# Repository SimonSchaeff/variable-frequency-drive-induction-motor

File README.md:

# Frequency Inverter – University Project

This repository contains the development files for a custom-built frequency inverter developed as part of a university project at Munich University of Applied Sciences (Hochschule München).

The power electronics and control electronics were designed using KiCad. The corresponding hardware design files are located in the `hardware/` directory. The software is based on an STM32 microcontroller, and the firmware source code is available in the `source_code/` directory.

The frequency inverter is designed to control asynchronous motors with a power rating of up to 3 kW. The operating frequency can be set within a range of 0 to 99 Hz, either manually using a potentiometer or wirelessly via a Bluetooth-enabled smartphone application. The application is located in the `smartphone_app/` directory.

## Disclaimer

This project is intended for educational and engineering development purposes. No warranty is provided regarding the functionality, safety, or suitability of the design for a particular application.

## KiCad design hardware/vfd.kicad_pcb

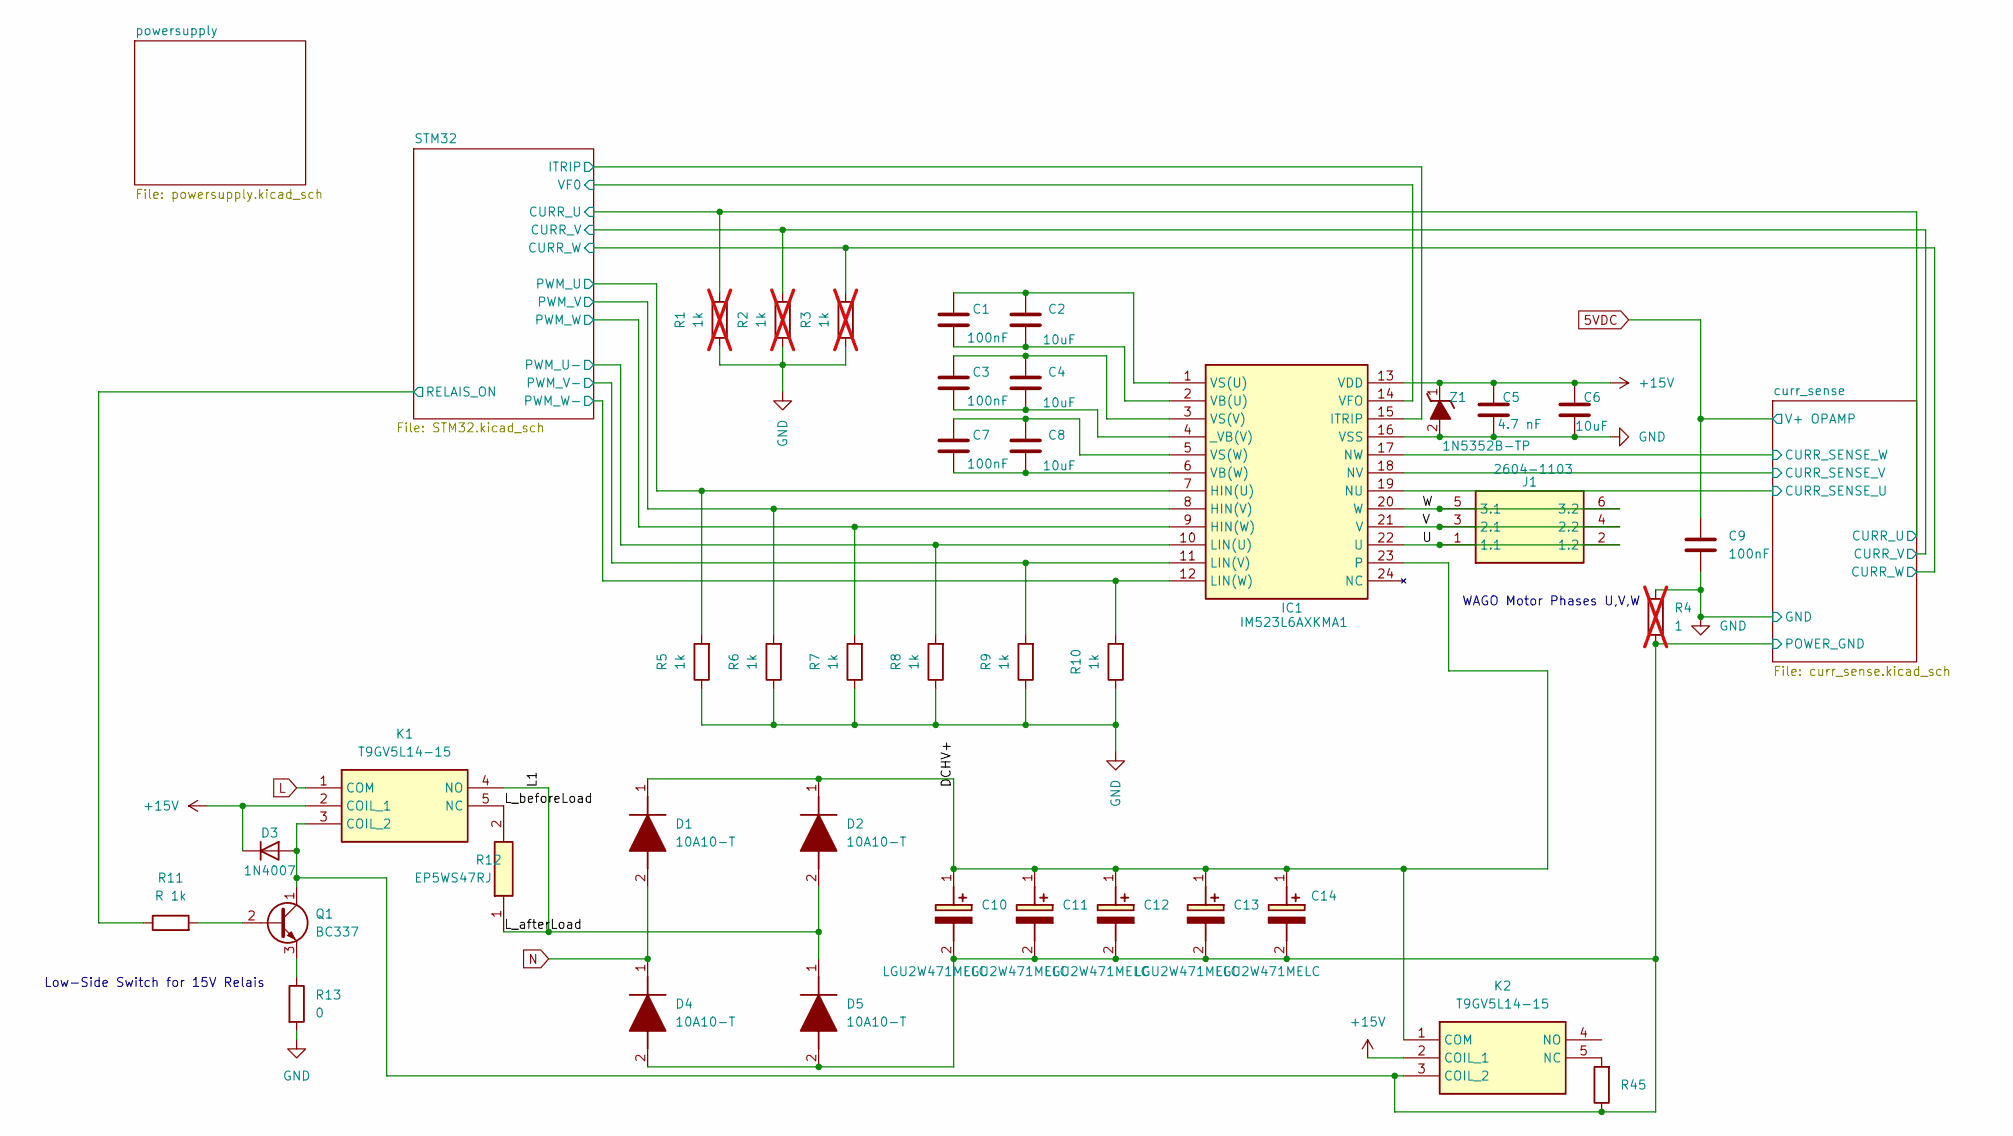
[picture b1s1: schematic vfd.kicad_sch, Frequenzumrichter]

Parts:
C1, C3, C7, C9: 100nF; C_0603_1608Metric
C2, C4, C6, C8: 10uF; C_1206_3216Metric
C5: 4.7 nF; C_0603_1608Metric
C10, C11, C12, C13, C14: LGU2W471MELC; CAPPRD1000W190D3550H5200; Mouser Part Number 647-LGU2W471MELC
D1, D2, D4, D5: 10A10-T; DIOAD4425W130L885D885; Mouser Part Number 583-10A10
D3: 1N4007; D_DO-41_SOD81_P10.16mm_Horizontal
IC1: IM523L6AXKMA1; Manufacturer_Part_Number IM523L6AXKMA1; Mouser Part Number 726-IM523L6AXKMA1
J1: 2604-1103; 26041103; Manufacturer_Part_Number 2604-1103
K1, K2: T9GV5L14-15; T9GV5L1415; Mouser Part Number 655-T9GV5L14-15
Q1: BC337; TO-92_Inline
R1, R2, R3: 1k; R_0603_1608Metric; not fitted
R4: 1; R_0603_1608Metric; not fitted
R5, R6, R7, R8, R9, R10: 1k; R_0603_1608Metric
R11: R 1k; R_0603_1608Metric
R12: EP5WS47RJ; RESAD5900W80L2500D850; Manufacturer_Part_Number EP5WS47RJ; Mouser Part Number 279-EP5WS47RJ
R13: 0; R_0603_1608Metric
R45: R_0603_1608Metric
Z1: 1N5352B-TP; DIOAD1910W90L670D310; Mouser Part Number 833-1N5352B-TP

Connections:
5VDC: C9.1; also elsewhere on the board
+15V: C5.1, C6.1, D3.1 (K), IC1.13 (VDD), K1.2 (COIL_1), K2.2 (COIL_1), Z1.1 (K); also elsewhere on the board
/DCHV+: C10.1 (+), C11.1 (+), C12.1 (+), C13.1 (+), C14.1 (+), D1.1 (K), D2.1 (K), IC1.23, K2.1 (COM)
/L1: D2.2 (A), D5.1 (K), K1.4 (NO), R12.1
/L_beforeLoad: K1.5 (NC), R12.2
/STM32/CURR_U: R1.2; also elsewhere on the board
/STM32/CURR_V: R2.2; also elsewhere on the board
/STM32/CURR_W: R3.2; also elsewhere on the board
/STM32/ITRIP: IC1.15 (ITRIP); also elsewhere on the board
/STM32/PWM_U: IC1.7 (HIN(U)), R5.2; also elsewhere on the board
/STM32/PWM_U-: IC1.10 (LIN(U)), R8.2; also elsewhere on the board
/STM32/PWM_V: IC1.8 (HIN(V)), R6.2; also elsewhere on the board
/STM32/PWM_V-: IC1.11 (LIN(V)), R9.2; also elsewhere on the board
/STM32/PWM_W: IC1.9 (HIN(W)), R7.2; also elsewhere on the board
/STM32/PWM_W-: IC1.12 (LIN(W)), R10.2; also elsewhere on the board
/STM32/RELAIS_ON: R11.1; also elsewhere on the board
/STM32/VF0: IC1.14 (VFO); also elsewhere on the board
/U: IC1.22 (U), J1.1 (1.1), J1.2 (1.2)
/V: IC1.21 (V), J1.3 (2.1), J1.4 (2.2)
/W: IC1.20 (W), J1.5 (3.1), J1.6 (3.2)
/curr_sense/CURR_SENSE_U: IC1.19 (NU); also elsewhere on the board
/curr_sense/CURR_SENSE_V: IC1.18 (NV); also elsewhere on the board
/curr_sense/CURR_SENSE_W: IC1.17 (NW); also elsewhere on the board
GND: C5.2, C6.2, C9.2, IC1.16 (VSS), R1.1, R2.1, R3.1, R4.2, R5.1, R6.1, R7.1, R8.1, R9.1, R10.1, R13.2, Z1.2 (A); also elsewhere on the board
L: K1.1 (COM); also elsewhere on the board
N: D1.2 (A), D4.1 (K); also elsewhere on the board
unnamed: C1.2, C2.2, IC1.2 (VB(U))
unnamed: C7.2, C8.2, IC1.6 (VB(W))
unnamed: C1.1, C2.1, IC1.1 (VS(U))
unnamed: C3.1, C4.1, IC1.3 (VS(V))
unnamed: C7.1, C8.1, IC1.5 (VS(W))
unnamed: C3.2, C4.2, IC1.4 (_VB(V))
unnamed: K2.5 (NC), R45.2
unnamed: Q1.2 (B), R11.2
unnamed: Q1.3 (E), R13.1

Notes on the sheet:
WAGO Motor Phases U,V,W
Low-Side Switch for 15V Relais

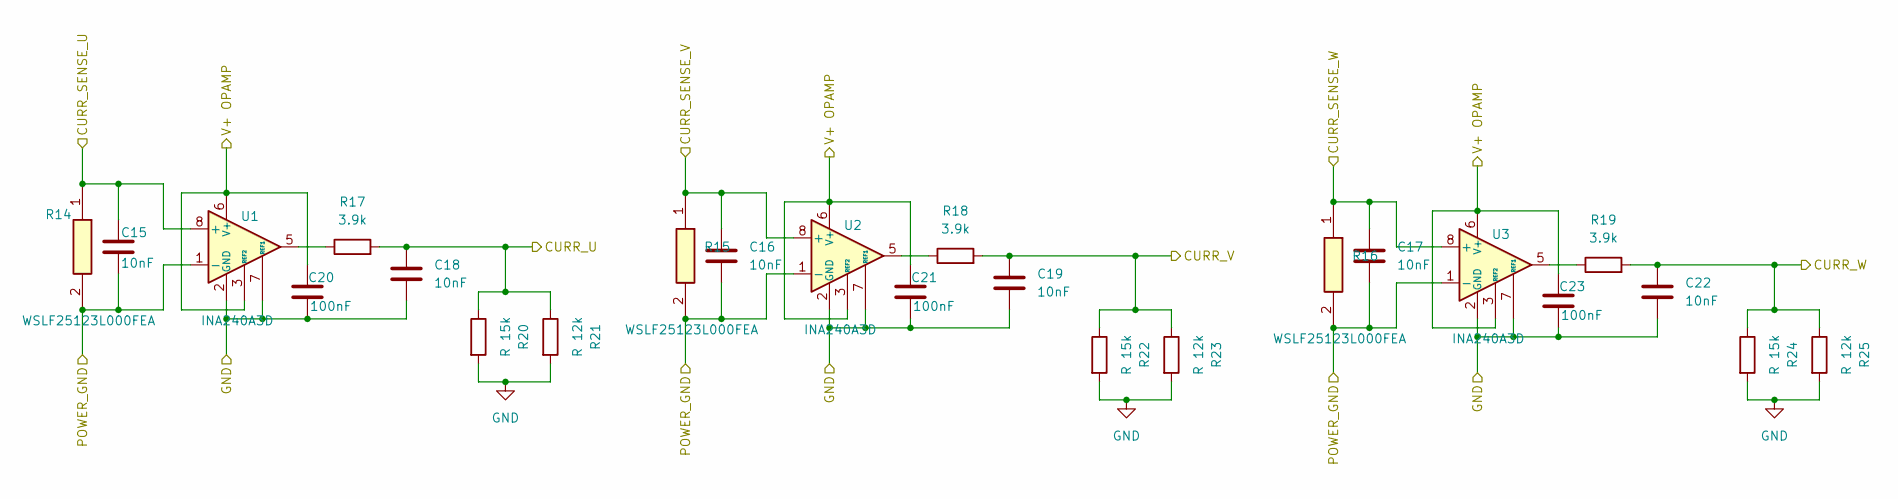
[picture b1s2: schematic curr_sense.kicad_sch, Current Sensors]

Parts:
C15, C16, C17, C18, C19, C22: 10nF; C_0603_1608Metric
C20, C21, C23: 100nF; C_0603_1608Metric
R14, R15, R16: WSLF25123L000FEA; RESC6430X48N; Mouser Part Number 71-WSLF25123L000FEA
R17, R18, R19: 3.9k; R_0603_1608Metric
R20, R22, R24: R 15k; R_0603_1608Metric
R21, R23, R25: R 12k; R_0603_1608Metric
U1, U2, U3: INA240A3D; SOIC-8_3.9x4.9mm_P1.27mm

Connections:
5VDC: C20.1, C21.1, C23.1, U1.3 (REF2), U1.6 (V+), U2.3 (REF2), U2.6 (V+), U3.3 (REF2), U3.6 (V+); also elsewhere on the board
/STM32/CURR_U: C18.1, R17.2, R20.1, R21.1; also elsewhere on the board
/STM32/CURR_V: C19.1, R18.2, R22.1, R23.1; also elsewhere on the board
/STM32/CURR_W: C22.1, R19.2, R24.1, R25.1; also elsewhere on the board
/curr_sense/CURR_SENSE_U: C15.1, R14.1, U1.8 (+); also elsewhere on the board
/curr_sense/CURR_SENSE_V: C16.1, R15.1, U2.8 (+); also elsewhere on the board
/curr_sense/CURR_SENSE_W: C17.1, R16.1, U3.8 (+); also elsewhere on the board
GND: C18.2, C19.2, C20.2, C21.2, C22.2, C23.2, R20.2, R21.2, R22.2, R23.2, R24.2, R25.2, U1.2 (GND), U1.4 (GND), U1.7 (REF1), U2.2 (GND), U2.4 (GND), U2.7 (REF1), U3.2 (GND), U3.4 (GND), U3.7 (REF1); also elsewhere on the board
unnamed: R17.1, U1.5
unnamed: R18.1, U2.5
unnamed: R19.1, U3.5

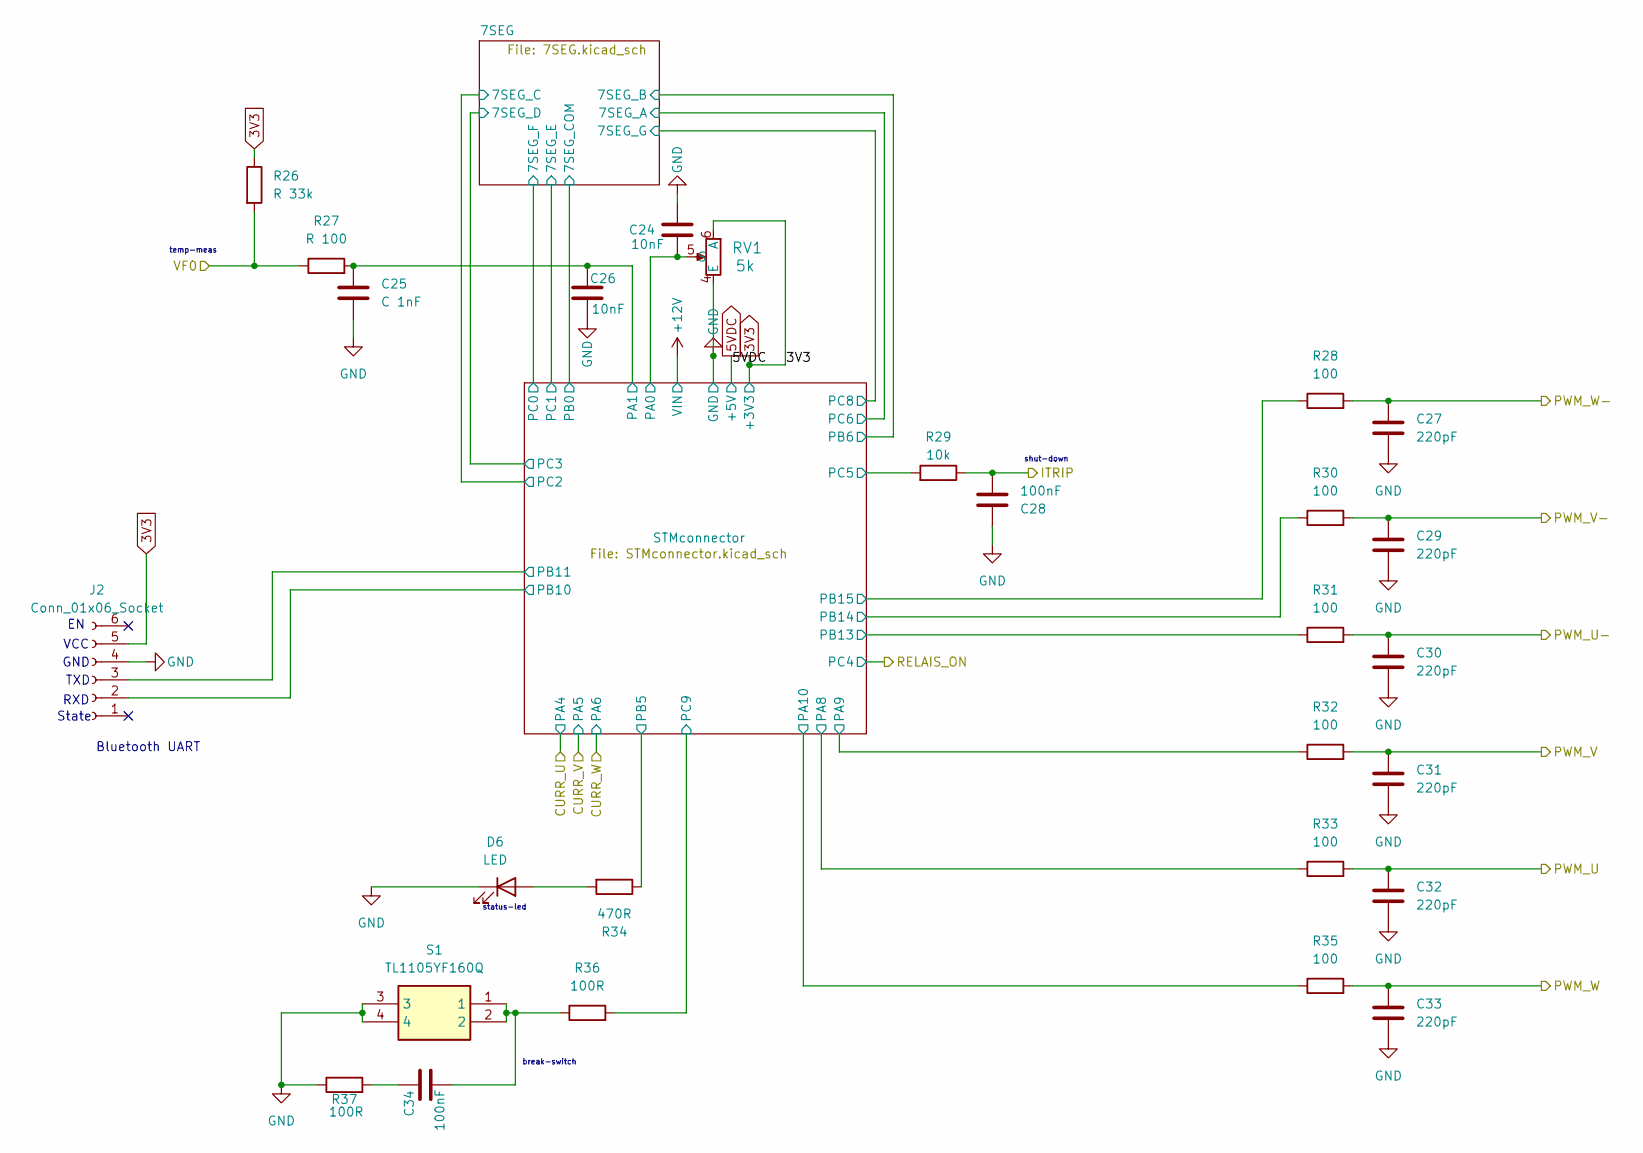
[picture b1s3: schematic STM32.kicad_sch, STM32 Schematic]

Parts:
C24, C26: 10nF; C_0603_1608Metric
C25: C 1nF; C_0603_1608Metric
C27, C29, C30, C31, C32, C33: 220pF; C_0603_1608Metric
C28, C34: 100nF; C_0603_1608Metric
D6: LED; LED_0805_2012Metric
J2: Conn_01x06_Socket; PinSocket_1x06_P2.54mm_Vertical
R26: R 33k; R_0603_1608Metric
R27: R 100; R_0603_1608Metric
R28, R30, R31, R32, R33, R35: 100; R_0603_1608Metric
R29: 10k; R_0603_1608Metric
R34: 470R; R_0603_1608Metric
R36, R37: 100R; R_0603_1608Metric
RV1: 5k; PC16SV-10IP06-103A2020-TA_PHR
S1: TL1105YF160Q; Mouser Part Number 612-TL1105YF160Q

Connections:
3V3: J2.5, R26.1, RV1.6 (A); also elsewhere on the board
/STM32/ITRIP: C28.2, R29.1; also elsewhere on the board
/STM32/PWM_U: C32.1, R33.2; also elsewhere on the board
/STM32/PWM_U-: C30.1, R31.2; also elsewhere on the board
/STM32/PWM_V: C31.1, R32.2; also elsewhere on the board
/STM32/PWM_V-: C29.1, R30.2; also elsewhere on the board
/STM32/PWM_W: C33.1, R35.2; also elsewhere on the board
/STM32/PWM_W-: C27.1, R28.2; also elsewhere on the board
/STM32/STMconnector/PA0: C24.1, RV1.5 (S); also elsewhere on the board
/STM32/STMconnector/PA1: C25.2, C26.1, R27.2; also elsewhere on the board
/STM32/STMconnector/PA8: R33.1; also elsewhere on the board
/STM32/STMconnector/PA9: R32.1; also elsewhere on the board
/STM32/STMconnector/PA10: R35.1; also elsewhere on the board
/STM32/STMconnector/PB5: R34.1; also elsewhere on the board
/STM32/STMconnector/PB10: J2.2; also elsewhere on the board
/STM32/STMconnector/PB11: J2.3; also elsewhere on the board
/STM32/STMconnector/PB13: R31.1; also elsewhere on the board
/STM32/STMconnector/PB14: R30.1; also elsewhere on the board
/STM32/STMconnector/PB15: R28.1; also elsewhere on the board
/STM32/STMconnector/PC5: R29.2; also elsewhere on the board
/STM32/STMconnector/PC9: R36.2; also elsewhere on the board
/STM32/VF0: R26.2, R27.1; also elsewhere on the board
GND: C24.2, C25.1, C26.2, C27.2, C28.1, C29.2, C30.2, C31.2, C32.2, C33.2, D6.1 (K), J2.4, R37.1, RV1.4 (E), S1.3, S1.4; also elsewhere on the board
unnamed: C34.1, R37.2
unnamed: C34.2, R36.1, S1.1, S1.2
unnamed: D6.2 (A), R34.2

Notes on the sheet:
Bluetooth UART
shut-down
RXD
break-switch
GND
temp-meas
State
VCC
status-led
TXD

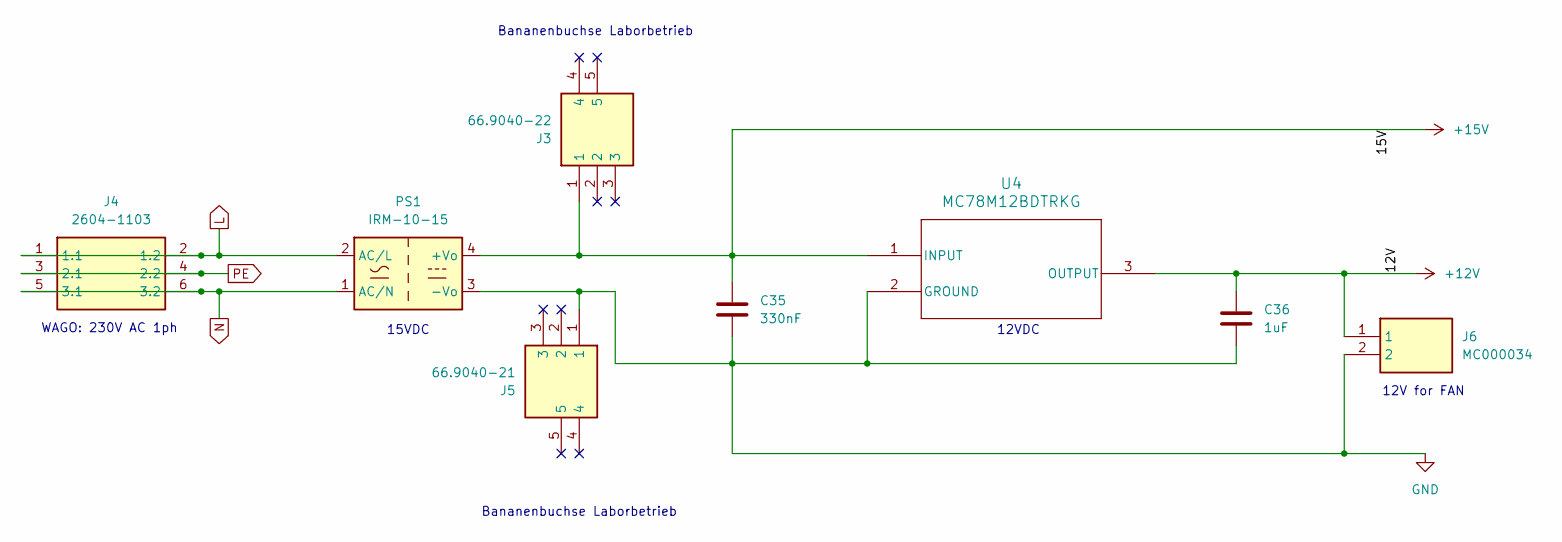
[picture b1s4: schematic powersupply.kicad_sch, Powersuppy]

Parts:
C35: 330nF; C_0603_1608Metric
C36: 1uF; C_0603_1608Metric
J3: 66.9040-22; 66904022; Manufacturer_Part_Number 66.9040-22
J4: 2604-1103; 26041103; Manufacturer_Part_Number 2604-1103
J5: 66.9040-21; 66904021; Manufacturer_Part_Number 66.9040-21
J6: MC000034; Manufacturer_Part_Number MC000034
PS1: IRM-10-15; Converter_ACDC_MeanWell_IRM-10-xx_THT
U4: MC78M12BDTRKG; DPAK-3_ONS

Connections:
+12V: C36.1, J6.1, U4.3 (OUTPUT); also elsewhere on the board
+15V: C35.1, J3.1 (1_1), PS1.4 (+Vo), U4.1 (INPUT); also elsewhere on the board
GND: C35.2, C36.2, J5.1 (1_1), J6.2, PS1.3 (-Vo), U4.2 (GROUND); also elsewhere on the board
L: J4.1 (1.1), J4.2 (1.2), PS1.2 (AC/L); also elsewhere on the board
N: J4.5 (3.1), J4.6 (3.2), PS1.1 (AC/N); also elsewhere on the board
PE: J4.3 (2.1), J4.4 (2.2)

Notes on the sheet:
WAGO: 230V AC 1ph
12VDC
Bananenbuchse Laborbetrieb
15VDC
12V for FAN

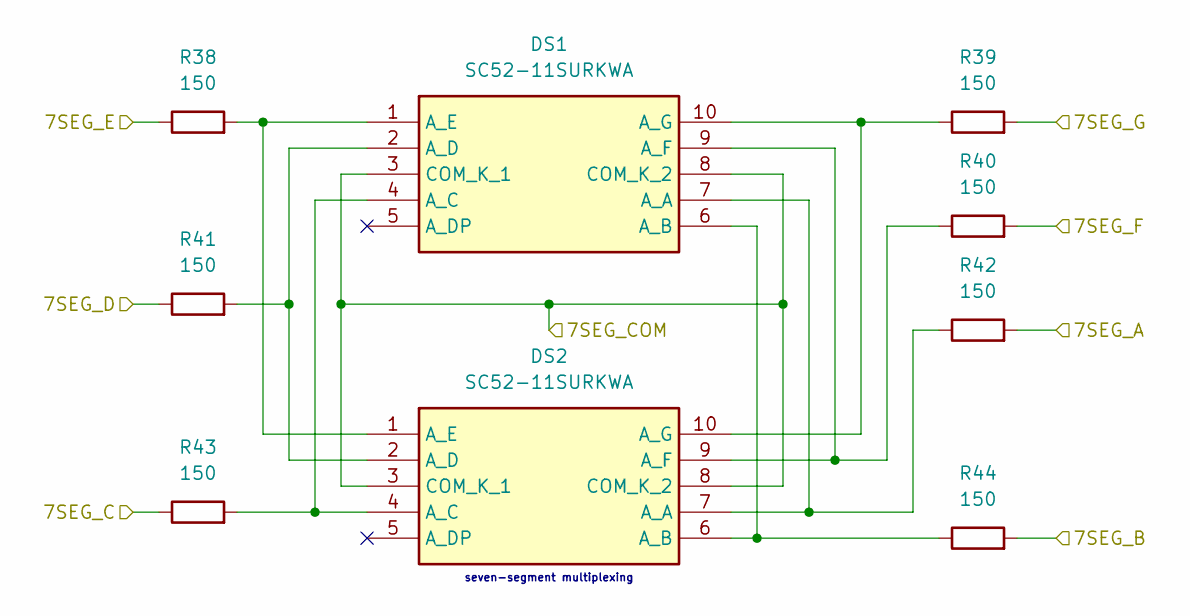
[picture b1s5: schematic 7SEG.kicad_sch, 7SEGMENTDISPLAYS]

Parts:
DS1, DS2: SC52-11SURKWA; SC5211SURKWA; Manufacturer_Part_Number SC52-11SURKWA; Mouser Part Number 604-SC5211SURKWA
R38, R39, R40, R41, R42, R43, R44: 150; R_0603_1608Metric

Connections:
/STM32/7SEG/7SEG_A: R42.2; also elsewhere on the board
/STM32/7SEG/7SEG_B: R44.2; also elsewhere on the board
/STM32/7SEG/7SEG_C: R43.1; also elsewhere on the board
/STM32/7SEG/7SEG_COM: DS1.3 (COM_K_1), DS1.8 (COM_K_2), DS2.3 (COM_K_1), DS2.8 (COM_K_2); also elsewhere on the board
/STM32/7SEG/7SEG_D: R41.1; also elsewhere on the board
/STM32/7SEG/7SEG_E: R38.1; also elsewhere on the board
/STM32/7SEG/7SEG_F: R40.2; also elsewhere on the board
/STM32/7SEG/7SEG_G: R39.2; also elsewhere on the board
unnamed: DS1.7 (A_A), DS2.7 (A_A), R42.1
unnamed: DS1.6 (A_B), DS2.6 (A_B), R44.1
unnamed: DS1.4 (A_C), DS2.4 (A_C), R43.2
unnamed: DS1.2 (A_D), DS2.2 (A_D), R41.2
unnamed: DS1.1 (A_E), DS2.1 (A_E), R38.2
unnamed: DS1.9 (A_F), DS2.9 (A_F), R40.1
unnamed: DS1.10 (A_G), DS2.10 (A_G), R39.1

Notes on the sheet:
seven-segment multiplexing

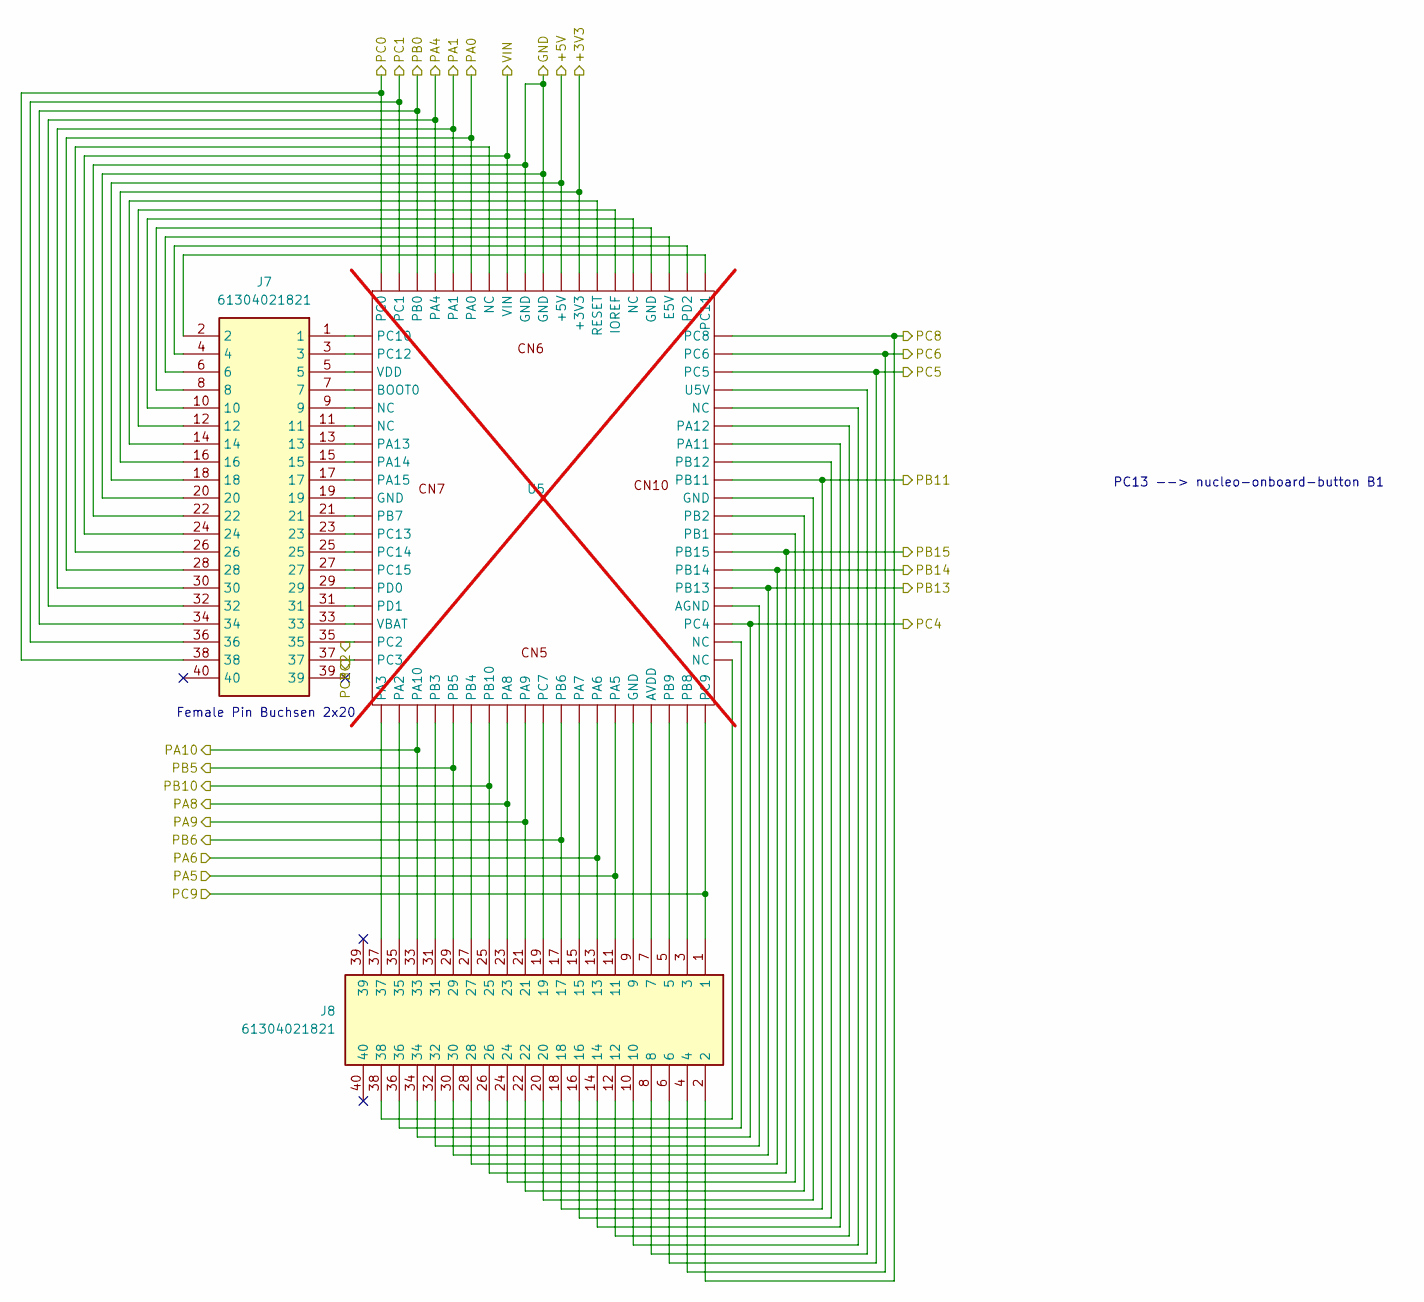
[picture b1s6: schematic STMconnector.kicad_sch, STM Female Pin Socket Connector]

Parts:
J7, J8: 61304021821; RHDR40W97P254X254_2X20_5130X508X860P; Manufacturer_Part_Number 61304021821; Mouser Part Number 710-61304021821
U5: not fitted

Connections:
3V3: J7.16, U5.; also elsewhere on the board
5VDC: J7.18, U5.; also elsewhere on the board
+12V: J7.24, U5.; also elsewhere on the board
/STM32/7SEG/7SEG_A: J8.4, U5.; also elsewhere on the board
/STM32/7SEG/7SEG_B: J8.17, U5.; also elsewhere on the board
/STM32/7SEG/7SEG_C: J7.35, U5.; also elsewhere on the board
/STM32/7SEG/7SEG_COM: J7.34, U5.; also elsewhere on the board
/STM32/7SEG/7SEG_D: J7.37, U5.; also elsewhere on the board
/STM32/7SEG/7SEG_E: J7.36, U5.; also elsewhere on the board
/STM32/7SEG/7SEG_F: J7.38, U5.; also elsewhere on the board
/STM32/7SEG/7SEG_G: J8.2, U5.; also elsewhere on the board
/STM32/CURR_U: J7.32, U5.; also elsewhere on the board
/STM32/CURR_V: J8.11, U5.; also elsewhere on the board
/STM32/CURR_W: J8.13, U5.; also elsewhere on the board
/STM32/RELAIS_ON: J8.34, U5.; also elsewhere on the board
/STM32/STMconnector/PA0: J7.28, U5.; also elsewhere on the board
/STM32/STMconnector/PA1: J7.30, U5.; also elsewhere on the board
/STM32/STMconnector/PA8: J8.23, U5.; also elsewhere on the board
/STM32/STMconnector/PA9: J8.21, U5.; also elsewhere on the board
/STM32/STMconnector/PA10: J8.33, U5.; also elsewhere on the board
/STM32/STMconnector/PB5: J8.29, U5.; also elsewhere on the board
/STM32/STMconnector/PB10: J8.25, U5.; also elsewhere on the board
/STM32/STMconnector/PB11: J8.18, U5.; also elsewhere on the board
/STM32/STMconnector/PB13: J8.30, U5.; also elsewhere on the board
/STM32/STMconnector/PB14: J8.28, U5.; also elsewhere on the board
/STM32/STMconnector/PB15: J8.26, U5.; also elsewhere on the board
/STM32/STMconnector/PC5: J8.6, U5.; also elsewhere on the board
/STM32/STMconnector/PC9: J8.1, U5.; also elsewhere on the board
GND: J7.20, J7.22, U5.; also elsewhere on the board
unnamed: J7.1, U5.
unnamed: J7.2, U5.
unnamed: J7.3, U5.
unnamed: J7.4, U5.
unnamed: J7.5, U5.
unnamed: J7.6, U5.
unnamed: J7.7, U5.
unnamed: J7.8, U5.
unnamed: J7.9, U5.
unnamed: J7.10, U5.
unnamed: J7.11, U5.
unnamed: J7.12, U5.
unnamed: J7.13, U5.
unnamed: J7.14, U5.
unnamed: J7.15, U5.
unnamed: J7.17, U5.
unnamed: J7.19, U5.
unnamed: J7.21, U5.
unnamed: J7.23, U5.
unnamed: J7.25, U5.
unnamed: J7.26, U5.
unnamed: J7.27, U5.
unnamed: J7.29, U5.
unnamed: J7.31, U5.
unnamed: J7.33, U5.
unnamed: J8.3, U5.
unnamed: J8.5, U5.
unnamed: J8.7, U5.
unnamed: J8.8, U5.
unnamed: J8.9, U5.
unnamed: J8.10, U5.
unnamed: J8.12, U5.
unnamed: J8.14, U5.
unnamed: J8.15, U5.
unnamed: J8.16, U5.
unnamed: J8.19, U5.
unnamed: J8.20, U5.
unnamed: J8.22, U5.
unnamed: J8.24, U5.
unnamed: J8.27, U5.
unnamed: J8.31, U5.
unnamed: J8.32, U5.
unnamed: J8.35, U5.
unnamed: J8.36, U5.
unnamed: J8.37, U5.
unnamed: J8.38, U5.

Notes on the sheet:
PC13 --> nucleo-onboard-button B1
Female Pin Buchsen 2x20

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
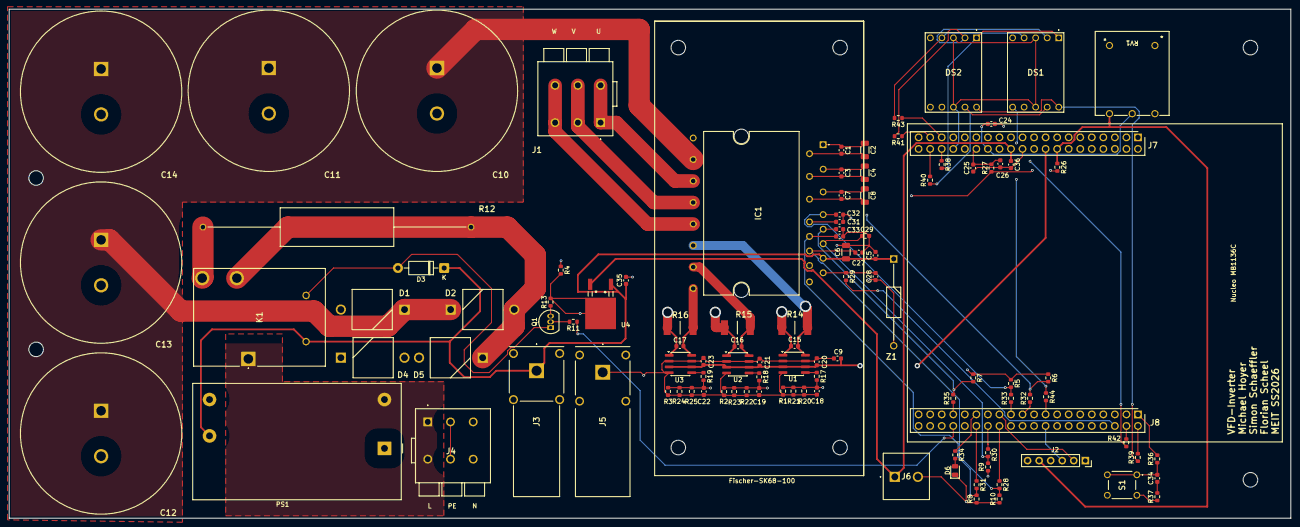
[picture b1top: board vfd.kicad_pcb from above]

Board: 4 copper layers, 282.0 x 112.0 mm, 107 parts (0 on the bottom side), 73 nets.

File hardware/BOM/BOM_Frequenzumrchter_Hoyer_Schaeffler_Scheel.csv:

"","Sourced","Placed","References","Value","Footprint","Quantity"
1,"✓","✓","C1, C3, C7, C9, C20, C21, C23, C28, C34","100nF","C_0603_1608Metric",9
2,"✓","✓","C15, C16, C17, C18, C19, C22, C24, C26","10nF","C_0603_1608Metric",8
3,"✓","✓","C27, C29, C30, C31, C32, C33","220pF","C_0603_1608Metric",6
4,"✓","✓","C10, C11, C12, C13, C14","LGU2W471MELC","CAPPRD1000W190D3550H5200",5
5,"✓","✓","C2, C4, C6, C8","10uF","C_1206_3216Metric",4
6,"✓","✓","C5","4.7 nF","C_0603_1608Metric",1
7,"✓","✓","C25","C 1nF","C_0603_1608Metric",1
8,"✓","✓","C35","330nF","C_0603_1608Metric",1
9,"✓","✓","C36","1uF","C_0603_1608Metric",1
10,"✓","✓","R1, R2, R3, R5, R6, R7, R8, R9, R10","1k","R_0603_1608Metric",9
11,"✓","✓","R28, R30, R31, R32, R35, R36, R37",100,"R_0603_1608Metric",7
12,"✓","✓","R38, R39, R40, R41, R42, R43, R44",150,"R_0603_1608Metric",7
13,"✓","✓","R14, R15, R16","WSLF25123L000FEA","RESC6430X48N",3
14,"✓","✓","R17, R18, R19","3.9k","R_0603_1608Metric",3
15,"✓","✓","R20, R22, R24","R 15k","R_0603_1608Metric",3
16,"✓","✓","R21, R23, R25","R 12k","R_0603_1608Metric",3
17,"✓","✓","R29, R33","10k","R_0603_1608Metric",2
18,"✓","✓","R4",1,"R_0603_1608Metric",1
19,"✓","✓","R11","R 1k","R_0603_1608Metric",1
20,"✓","✓","R12","EP5WS47RJ","RESAD5900W80L2500D850",1
21,"✓","✓","R13","R 100k","R_0603_1608Metric",1
22,"✓","✓","R26","R 33k","R_0603_1608Metric",1
23,"✓","✓","R27","R 100","R_0603_1608Metric",1
24,"✓","✓","R34","470R","R_0603_1608Metric",1
25,"✓","✓","D1, D2, D4, D5","10A10-T","DIOAD4425W130L885D885",4
26,"✓","✓","D3","1N4007","D_DO-41_SOD81_P10.16mm_Horizontal",1
27,"✓","✓","D6","LED","LED_0805_2012Metric",1
28,"✓","✓","U1, U2, U3","INA240A3D","SOIC-8_3.9x4.9mm_P1.27mm",3
29,"✓","✓","U4","MC78M12BDTRKG","DPAK-3_ONS",1
30,"✓","✓","DS1, DS2","SC52-11SURKWA","SC5211SURKWA",2
31,"","","IC1","IM523L6AXKMA1","IM523L6AXKMA1",1
32,"✓","✓","K1","T9GV5L14-15","T9GV5L1415",1
33,"✓","✓","PS1","IRM-10-15","Converter_ACDC_MeanWell_IRM-10-xx_THT",1
34,"✓","✓","Q1","BC337","TO-92_Inline",1
35,"✓","✓","RV1","5k","PC16SV-10IP06-103A2020-TA_PHR",1
36,"✓","✓","S1","TL1105YF160Q","TL1105YF160Q",1
37,"✓","✓","Z1","1N5352B-TP","DIOAD1910W90L670D310",1
38,"✓","✓","J1, J4","2604-1103",26041103,2
39,"✓","✓","J7, J8",61304021821,"RHDR40W97P254X254_2X20_5130X508X860P",2
40,"✓","✓","J2","Conn_01x06_Socket","PinSocket_1x06_P2.54mm_Vertical",1
41,"✓","✓","J3","66.9040-22",66904022,1
42,"✓","✓","J5","66.9040-21",66904021,1
43,"✓","✓","J6","MC000034","MC000034",1

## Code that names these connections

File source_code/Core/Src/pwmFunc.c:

/*
 * pwmFunc.c
 *
 *  Project:    Hochschule Muenchen
 *  Created on: 2026-03-28
 *  Author:     Simon Schäffler
 *
 *  3-Phase SPWM for 6-switch inverter
 *  TIM3 Center-Aligned counter used as carrier signal
 *
 *  Output pins (gate driver handles inverse signal + dead-time):
 *    Phase A: PB10
 *    Phase B: PB4
 *    Phase C: PB3
 */

/* ============ Includes ============ */
#include "main.h"
#include "pwmFunc.h"
#include "gpioFunc.h"
#include "freqFunc.h"
#include "config.h"         /* operating mode: CFG_MODE_LAB / CFG_MODE_MAINS */

/* ============ Defines ============ */

/* --- Derived from config.h --- */
#define U_ZK_HALF     (CFG_U_ZK / 2)                                      /* [V]    DC link half voltage                       */
#define K_UF          ((float)CFG_U_NENN / (float)CFG_F_NENN)             /* [V/Hz] U/f slope (e.g. k = 230V / 50Hz = 4.6)     */
#define MOD_FACTOR    ((uint32_t)((K_UF * 32767.0f) / (float)U_ZK_HALF))  /* Q0.15 factor per Hz MOD_FACTOR = (k / (U_ZK / 2)) */
#define F_MAX         ((uint16_t)((float)U_ZK_HALF / K_UF))               /* [Hz]   max freq without overmod (m = 1)           */

/* 120° and 240° in Q0.15 angle format */
#define ANGLE_120DEG  (frac16_t)0x5555              /* 120° */
#define ANGLE_240DEG  (frac16_t)((sint16)0xAAAA)    /* 240° */

/* ============ Forward Declarations ============ */

static frac16_t  freqToAngleStep(uint16_t freqHz);
static frac16_t  freqToModIndex(uint16_t freqHz);

/* ============ Variables ============ */

static frac16_t s_angleStep = 0;   /* updated every 100µs in spwmUpdate() */
static frac16_t s_angle     = 0;                 /* current angle  */

/* Modulation index: 0x7FFF = 1.0 (max), 0x4000 = 0.5 */
static frac16_t s_modIndex  = 0;   /* updated every 100µs in spwmUpdate() */

/* Debug variables - visible in debugger */
volatile frac16_t spwm_u_a     = 0;
volatile frac16_t spwm_u_b     = 0;
volatile frac16_t spwm_u_c     = 0;
volatile sint16   spwm_carrier = 0;
/* volatile uint32_t taskCountpwmUpdate = 0; */

/* ============ Local Functions ============ */


/*
 * freqToAngleStep()
 * Converts Hz to Q0.15 angle increment per carrier-peak tick.
 * spwmUpdate() is called from TIM1 ISR at 5 kHz (72MHz / (2*7200)).
 * 2 * 'pi' = 65536 in Q0.15
 * angleStep = f * 65536 / 5000
 * Example: 50 Hz -> 655,  100 Hz -> 1311
 */
static frac16_t freqToAngleStep(uint16_t freqHz)
{
    return (frac16_t)((uint32_t)freqHz * 65536UL / 5000UL);
}

/*
 * freqToModIndex()
 *
 * U/f = const:  k = U_nenn / f_nenn  [V/Hz]  (see config.h)
 *               U_ref = k * f  [V]
 *
 * modIndex = U_ref / (U_ZK / 2)
 *
 * As Q0.15:
 *   modIndex_Q0.15 = f * MOD_FACTOR
 *
 * Overmodulation above F_MAX Hz -> clamp to 32767
 */
static frac16_t freqToModIndex(uint16_t freqHz)
{
    uint32_t mod = (uint32_t)freqHz * MOD_FACTOR;
    if (mod > 32767UL) mod = 32767UL;   /* clamp above F_MAX Hz */
    return (frac16_t)mod;
}


/* ============ Exported Functions ============ */

/*
 * spwmUpdate()
 * Called from TIM1 Update ISR at every carrier PEAK (CNT == ARR = 3600).
 * TIM1 Center-Aligned Mode 1 + URS=1 → ISR fires only at overflow (peak), 10 kHz.
 *
 * Writes CCR1/2/3 → TIM1 hardware comparator sets pins automatically:
 *   CNT < CCR  → CHx HIGH,  CHxN LOW
 *   CNT > CCR  → CHx LOW,   CHxN HIGH  (+ hardware deadtime ~1µs)
 *
 *   CH1/CH1N (PA8/PB13)  → Phase U
 *   CH2/CH2N (PA9/PB14)  → Phase V
 *   CH3/CH3N (PA10/PB15) → Phase W
 *
 * CCR = Period/2 + u * Period/2 / 32767
 *     = 1800 + u * 1800 / 32767
 */
void spwmUpdate(void)
{
    if (!brakeActive)
    {
        /* --- Update angle step and modulation index --- */
        s_angleStep = freqToAngleStep(freq_motor);
        s_modIndex  = freqToModIndex(freq_motor);

        /* --- Compute sine reference signals (Q0.15) --- */
        spwm_u_a = (frac16_t)(((int32_t)s_modIndex * MathF16_Sin(s_angle))                >> 15);
        spwm_u_b = (frac16_t)(((int32_t)s_modIndex * MathF16_Sin(s_angle - ANGLE_120DEG)) >> 15);
        spwm_u_c = (frac16_t)(((int32_t)s_modIndex * MathF16_Sin(s_angle - ANGLE_240DEG)) >> 15);

        /* --- Write CCR → hardware comparator + deadtime sets all 6 pins automatically --- */
        /* TIM1->CCR1 = (uint16_t)(3600 + ((int32_t)spwm_u_a * 3600L) / 32767L); */
        /* TIM1->CCR2 = (uint16_t)(3600 + ((int32_t)spwm_u_b * 3600L) / 32767L); */
        /* TIM1->CCR3 = (uint16_t)(3600 + ((int32_t)spwm_u_c * 3600L) / 32767L); */

        TIM1->CCR1 = (uint16_t)(3600 + (((int32_t)spwm_u_a * 3600L) >> 15));
        TIM1->CCR2 = (uint16_t)(3600 + (((int32_t)spwm_u_b * 3600L) >> 15));
        TIM1->CCR3 = (uint16_t)(3600 + (((int32_t)spwm_u_c * 3600L) >> 15));

        /* --- Advance angle --- */
        s_angle += s_angleStep;
    }
    
}

void spwmBrake(void)
{
    /* CCR = 0 → CNT always >= CCR → CHx LOW, CHxN HIGH (+ hardware dead time) */
    TIM1->CCR1 = 0;
    TIM1->CCR2 = 0;
    TIM1->CCR3 = 0;
    /* reset angle */
    s_angle      = 0;
    s_angleStep  = 0;
    /* setting frequency immediately to zero */
    freq_motor   = 0;
    freq_pref_user = 0;
}

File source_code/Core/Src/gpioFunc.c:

/*
 * gpioFunc.c
 *
 *  Project:    Hochschule Muenchen
 *  Created on: 2026-03-28
 *  Author:     Simon Schäffler
 */

#include "main.h"
#include "gpioFunc.h"
#include "pwmFunc.h"
#include "timerFunc.h"

/* ============ Variables ============ */

volatile bool brakeActive = false;

/* ============ Functions ============ */

void gpioInit(void)
{
	GPIO_InitTypeDef GPIO_InitStruct;

	/* --- Enable clocks --- */
	__HAL_RCC_GPIOA_CLK_ENABLE();
	__HAL_RCC_GPIOB_CLK_ENABLE();
	__HAL_RCC_GPIOC_CLK_ENABLE();

	/* --- LED0 (PB5) --- */
	GPIO_InitStruct.Mode  = GPIO_MODE_OUTPUT_PP;
	GPIO_InitStruct.Pull  = GPIO_NOPULL;
	GPIO_InitStruct.Speed = GPIO_SPEED_FREQ_LOW;
	GPIO_InitStruct.Pin   = LED0_Pin;
	HAL_GPIO_Init(LED0_GPIO_Port, &GPIO_InitStruct);
	HAL_GPIO_WritePin(LED0_GPIO_Port, LED0_Pin, GPIO_PIN_RESET);

	/* --- ITRIP (PC5) – digital output, default LOW --- */
	GPIO_InitStruct.Pin   = ITRIP_Pin;
	HAL_GPIO_Init(ITRIP_GPIO_Port, &GPIO_InitStruct);
	HAL_GPIO_WritePin(ITRIP_GPIO_Port, ITRIP_Pin, GPIO_PIN_RESET);

	/* --- RELAIS (PC4) – digital output, default LOW --- */
	GPIO_InitStruct.Pin   = RELAY_PIN;
	HAL_GPIO_Init(RELAY_PORT, &GPIO_InitStruct);
	HAL_GPIO_WritePin(RELAY_PORT, RELAY_PIN, GPIO_PIN_RESET); /* important: relay must be open at startup */

	/* --- BTN1 (PC9, EXTI9_5) --- */
	GPIO_InitStruct.Pin  = BTN1_Pin;
	GPIO_InitStruct.Mode = GPIO_MODE_IT_FALLING;
	GPIO_InitStruct.Pull = GPIO_PULLUP;   /* btn is low active */
	HAL_GPIO_Init(BTN1_GPIO_Port, &GPIO_InitStruct);
	HAL_NVIC_SetPriority(EXTI9_5_IRQn, BTN1_IRQ_PRIORITY, 0);
	HAL_NVIC_EnableIRQ(EXTI9_5_IRQn);
}

/* Button ISR – BTN1 on PC9 */
void EXTI9_5_IRQHandler(void)
{
	__HAL_GPIO_EXTI_CLEAR_FLAG(BTN1_Pin);

	/* Software debouncing: ignore triggers within 200ms of the last one.
	 * g_tim2Ticks runs in TIM2 ISR (priority 2) → independent of SysTick.
	 * 200ms = 2000 ticks at 100µs per tick. */
	static uint32_t s_lastTick = 0;
	if ((g_tim2Ticks - s_lastTick) < 2000U) return;
	s_lastTick = g_tim2Ticks;

	if (!brakeActive)
	{
		brakeActive = true;
		spwmBrake();
	}
	else
	{
		brakeActive = false;
	}
}

void gpioTogglePin(GPIO_TypeDef *port, uint16_t pin)
{
	HAL_GPIO_TogglePin(port, pin);
}

void gpioSetPin(GPIO_TypeDef *port, uint16_t pin, int on)
{
	HAL_GPIO_WritePin(port, pin, on ? GPIO_PIN_SET : GPIO_PIN_RESET);
}
